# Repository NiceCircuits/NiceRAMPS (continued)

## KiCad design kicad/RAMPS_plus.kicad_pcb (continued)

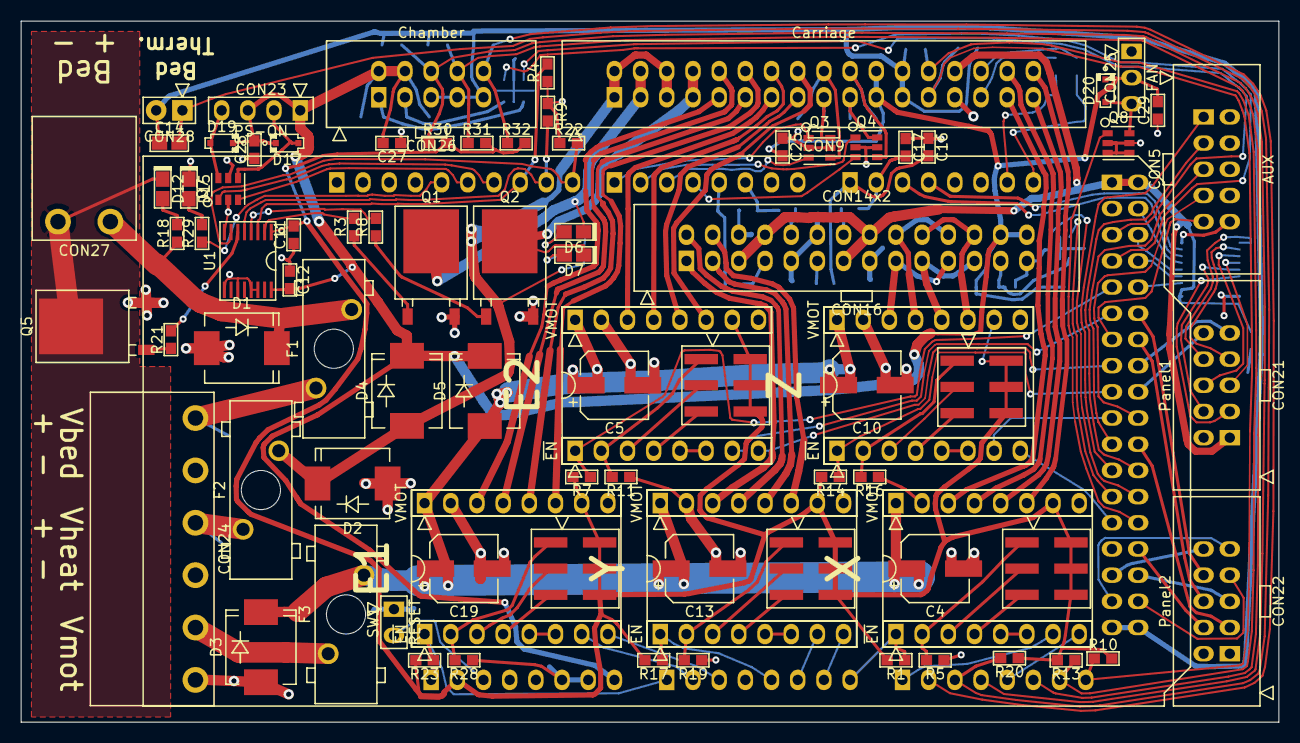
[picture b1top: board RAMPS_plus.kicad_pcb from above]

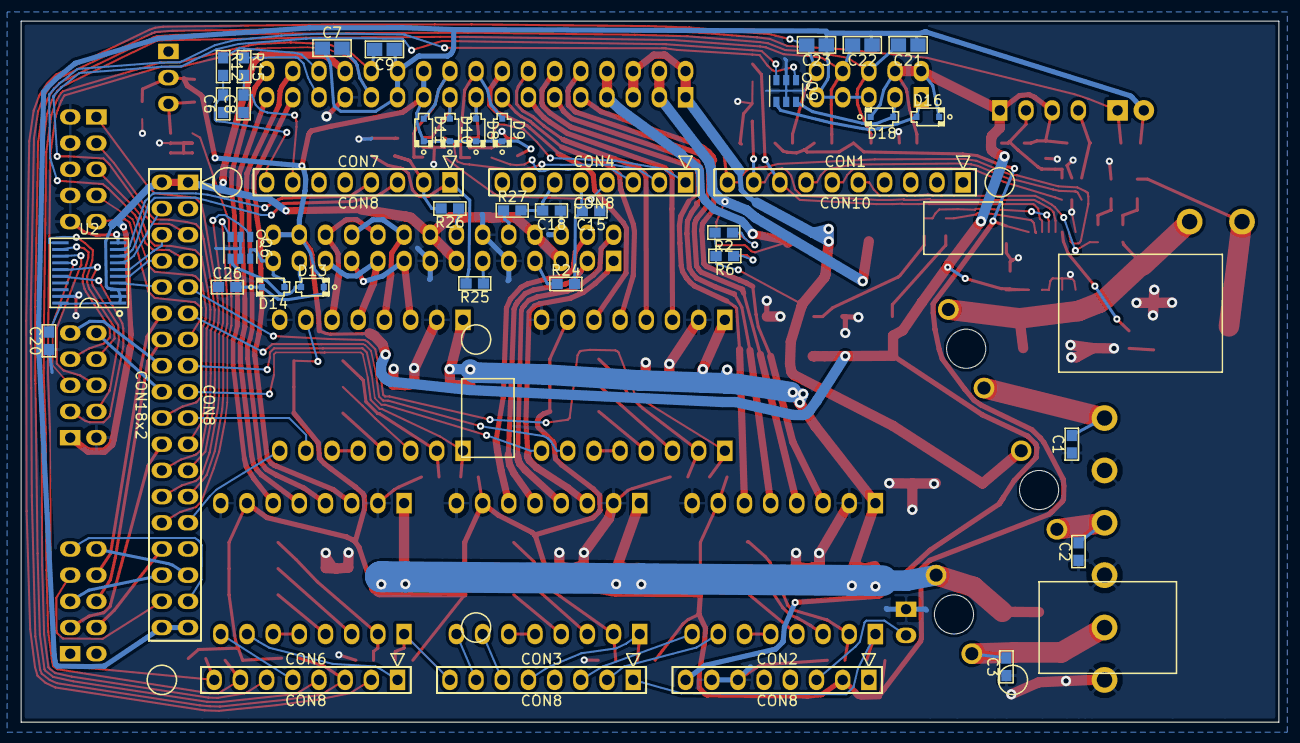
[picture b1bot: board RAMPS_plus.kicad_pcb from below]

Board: 2 copper layers, 122.0 x 68.0 mm, 134 parts (40 on the bottom side), 151 nets.

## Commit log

2014-04-08 Start draw schematic
    References: #1 #5
2014-04-08 Draw schematic
    References: #1 #5
2014-04-15 Draw schematic
    Added 40109 translators to drive MOSFET's.
    References: #1 #5 #13 #9
    Close #6
2014-04-16 Draw schematic
    Added sheet for panel connector and sheet for Y axis circuits.
    Added ULN2803
    References: #1 #11 #7 #5
    Close #13
2014-04-16 Draw schematic
    Commit before trying newer version of KiCad
2014-05-09 Draw schematic
    Finished redrawing basic RAMPS schematic
    References: #1 #4 #7 #15
    Close #5 #17 #18
2014-05-11 Change components to my own
    References: #1 #19
2014-05-22 Add YZ connector. Add endstop filters.
    Close #23
    References: #3 #20
2014-06-02 Add panel connectors. Minor ERC fixes.
    References: #11
2014-06-03 Change CD40109 to CD4504
2014-06-03 Add translators for LCD
    ref #11
2014-06-07 Change ULN2803 to discrete MOSFET's FDC6401N
    Close #7
2014-06-08 Extract power supply circuits to another sheet. Add power off circuit.
2014-06-08 Change stepstick signal voltage to IOREF.
    reference #9
    close #21
2014-06-08 Add AUX connectro for a few buttons or so
    close #14
2014-06-08 Added fan connectors for electronics and power supply
    close #15
2014-06-08 Add heated chamber support
    close #22
2014-06-12 Add footprint informations
2014-06-13 Place arduino shield connectors
2014-06-14 Place components
2014-06-14 Change jumpers to SMD
2014-06-14 Add bed connector. Routing.
2014-06-14 Change 1A diodes. Add capacitors next to OC outputs. Place.
2014-06-14 Place
2014-06-15 Fix panel connections. Place.
2014-06-15 Place. Add design rules (Merkar, 6/8mil)
2014-06-15 Add autorouted board (for reference)
2014-06-15 Start routing.
2014-06-15 Route.
2014-06-18 Routing
2014-06-22 Swap pins
2014-06-22 Route
2014-06-23 Exchange stepstick connections.
    Simplify layout
2014-06-23 Pin swap. Route.
2014-06-24 Add AGND. Route.
    close #27
2014-06-24 Route.
    Routed board with some minor DRC issues.
2014-06-24 To previous commit.
2014-06-26 Fix DRC issues.
2014-06-26 Route. Generate gerber.
2014-06-26 Fix vias. generate gerber.
2014-06-26 Organize silkscreen.
2014-06-26 Rename and delete files
2014-06-26 Gerber rename
